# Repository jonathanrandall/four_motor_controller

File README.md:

# NOTE

This was originally done in kicad 9.0 and updated to kicad 10.0. Need to check the symbol for the NMOS transistor against the data sheet for the transistor in the bom file

# four_motor_controller

A 4-layer PCB motor controller for robotics applications. Drives 4 DC motors with encoder feedback using an ESP32-S3 microcontroller, 
Inlcudes:
* 4× VNH7040AYTR high-current motor drivers, which is rated for 35A, but the current is limited by the board and not the motor driver. I'm using 2oz copper on the outer layers and 1oz copper on the inner layers, so this should provide ~12A continuous current on each motor driver; and a
* MCP23017 I2C GPIO expander for direction control.

The design files are for KiCad 10.0.

The ROS2 control code used in the video is at https://github.com/jonathanrandall/new_pcb_robot

## Repository Contents

```
hardware/                   # KiCad schematic, PCB layout, and project files
  symbols/                  # Custom KiCad symbol and footprint for VNH7040AYTR
docs_and_outputs/           # BOM (JLCPCB format), Gerbers (zip), PINMAP, and datasheets
firmware/esp32_bridge/      # PlatformIO firmware project (Arduino framework, C++17)
  src/                      # main.cpp, Motor, PIDController, QuadratureEncoder,
                            #   RobotController, Mcp23017Bus, WebDashboard, PanTiltController
  include/                  # Header files
  platformio.ini            # Build configuration
```

## Important Notes

**The BOM and PINMAP in `docs_and_outputs/` may be out of date.** Always cross-reference against the schematic and PCB files before ordering parts or assembling hardware.

**The custom VNH7040AYTR symbol/footprint** (`hardware/symbols/`) must be added to your KiCad library if opening the project on a new machine.

**The firmware has not been validated on hardware.** It compiles and is provided as a starting point.

**WiFi credentials are not included.** Before building the firmware, set your SSID and password in `firmware/esp32_bridge/src/main.cpp`.

## Building the Firmware

Requires [PlatformIO](https://platformio.org/). All commands run from `firmware/esp32_bridge/`.

```bash
# Build
pio run

# Flash (USB-C, use BOOT mode if required)
pio run --target upload

# Monitor serial output (115200 baud)
pio device monitor
```

## Contributing

Contributions are welcome. If you have your own motor controller design or variant you would like to share, please add it in its own directory rather than modifying the existing files. Pull requests with bug fixes or improvements to the existing design are welcome.

## Disclaimer

This hardware design is provided as-is, with no warranty of any kind. Anyone who uses, manufactures, or builds upon these files does so entirely at their own risk. The author accepts no responsibility for any damage to property, equipment, or persons resulting from the use of this design. Always verify the design independently before fabrication or use in any application.

## Licence

The hardware design files in this repository are licensed under the
CERN Open Hardware Licence Version 2 - Permissive (CERN-OHL-P-2.0).

See the `LICENSE` file for the full licence text.

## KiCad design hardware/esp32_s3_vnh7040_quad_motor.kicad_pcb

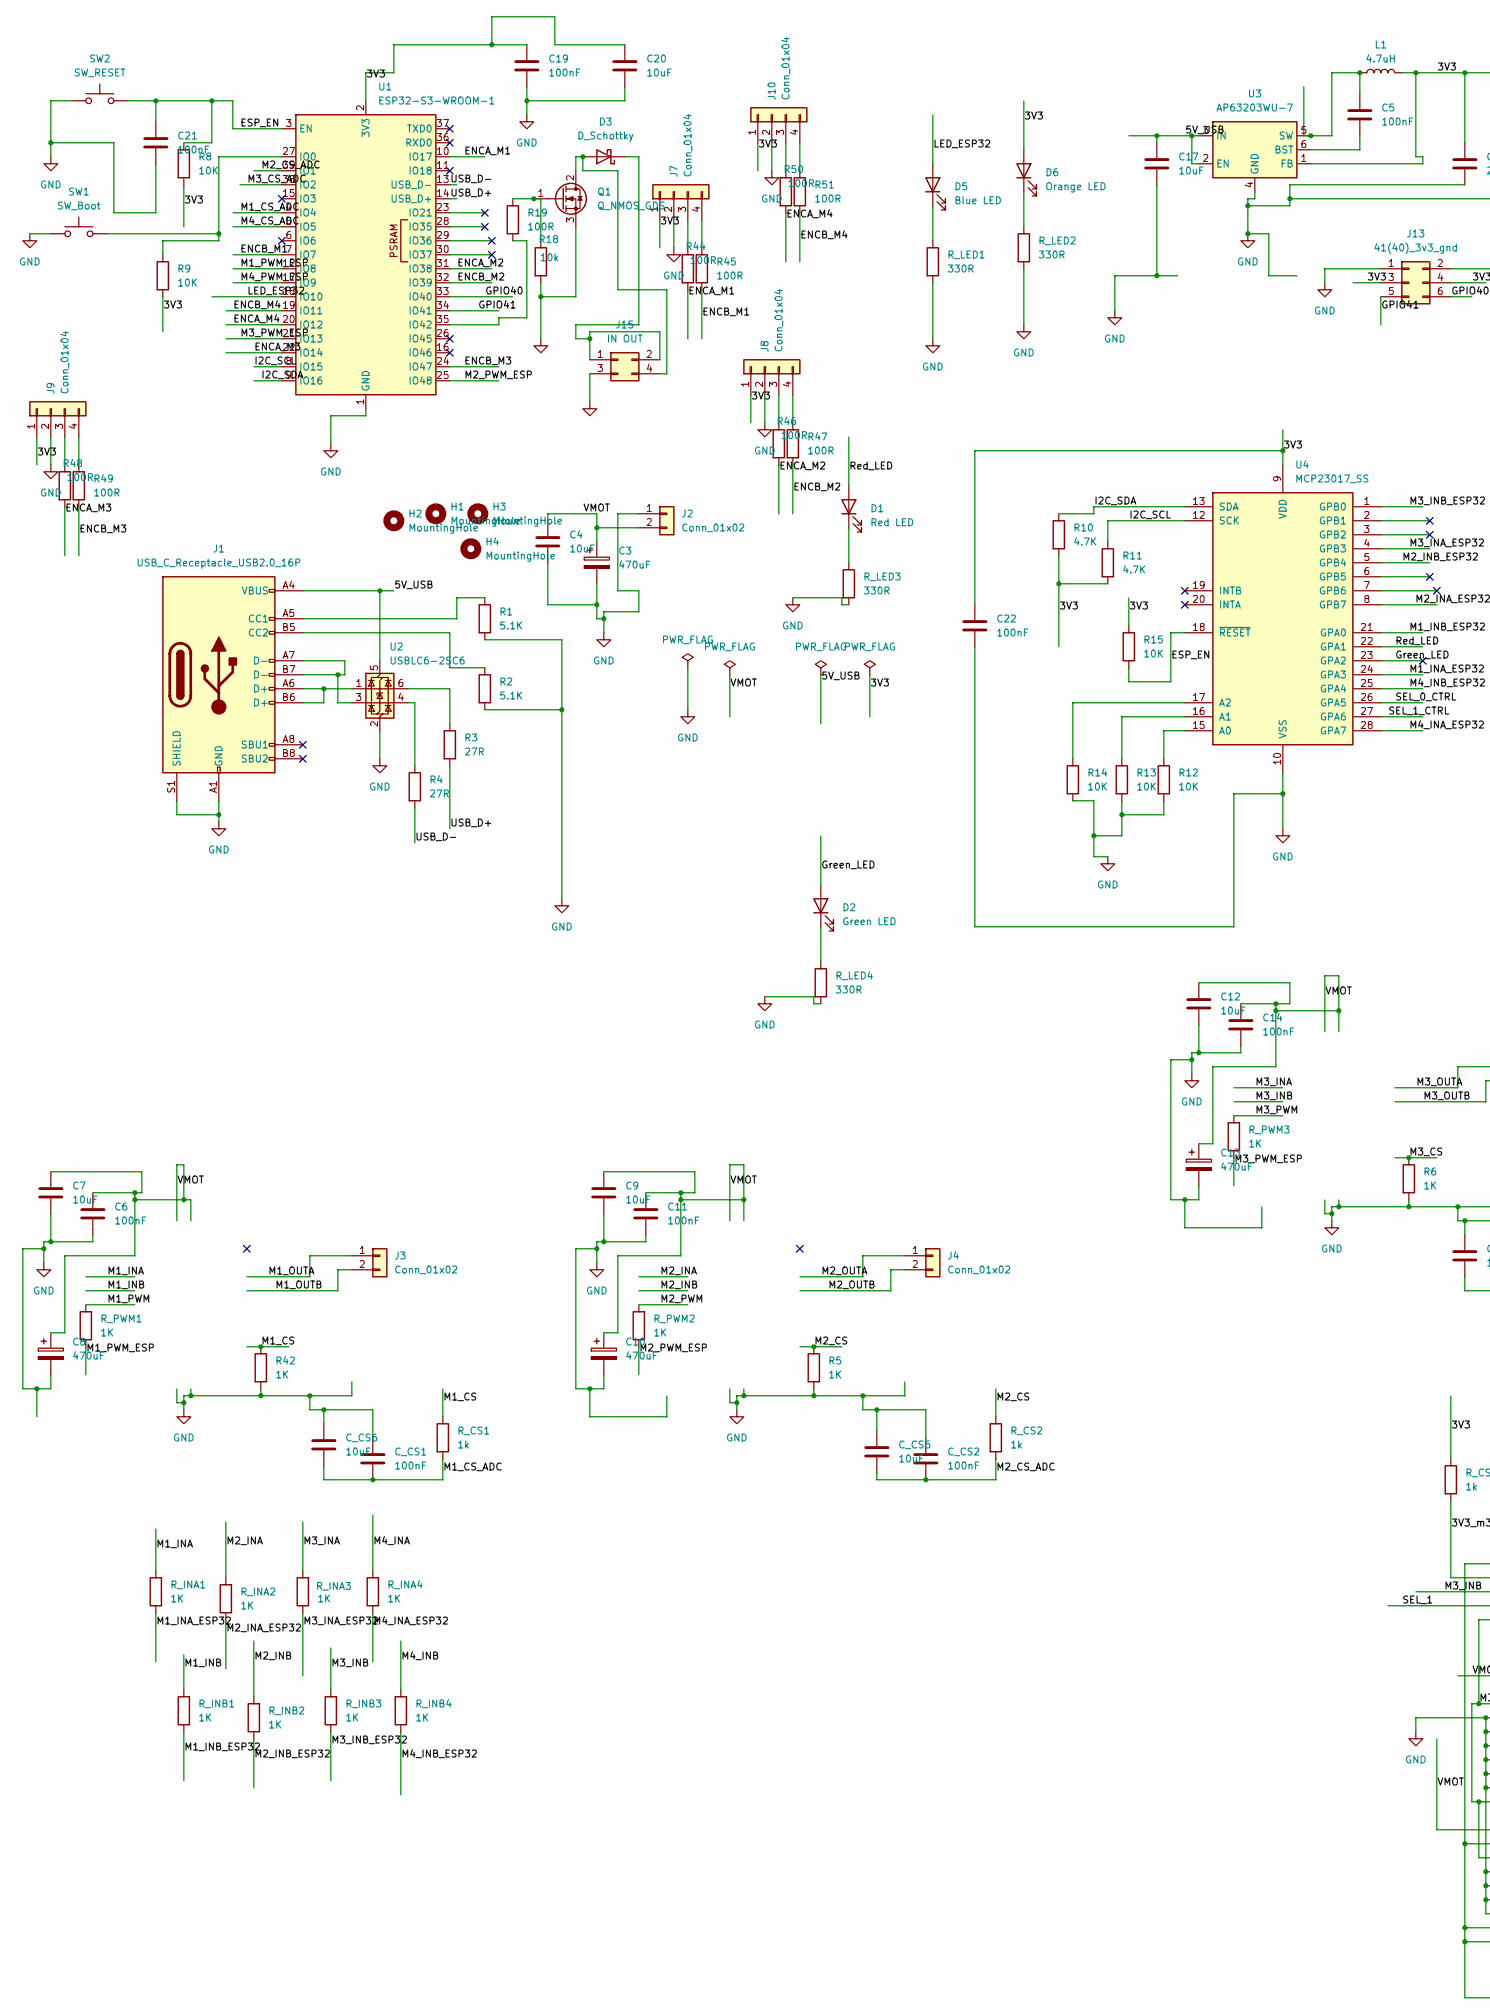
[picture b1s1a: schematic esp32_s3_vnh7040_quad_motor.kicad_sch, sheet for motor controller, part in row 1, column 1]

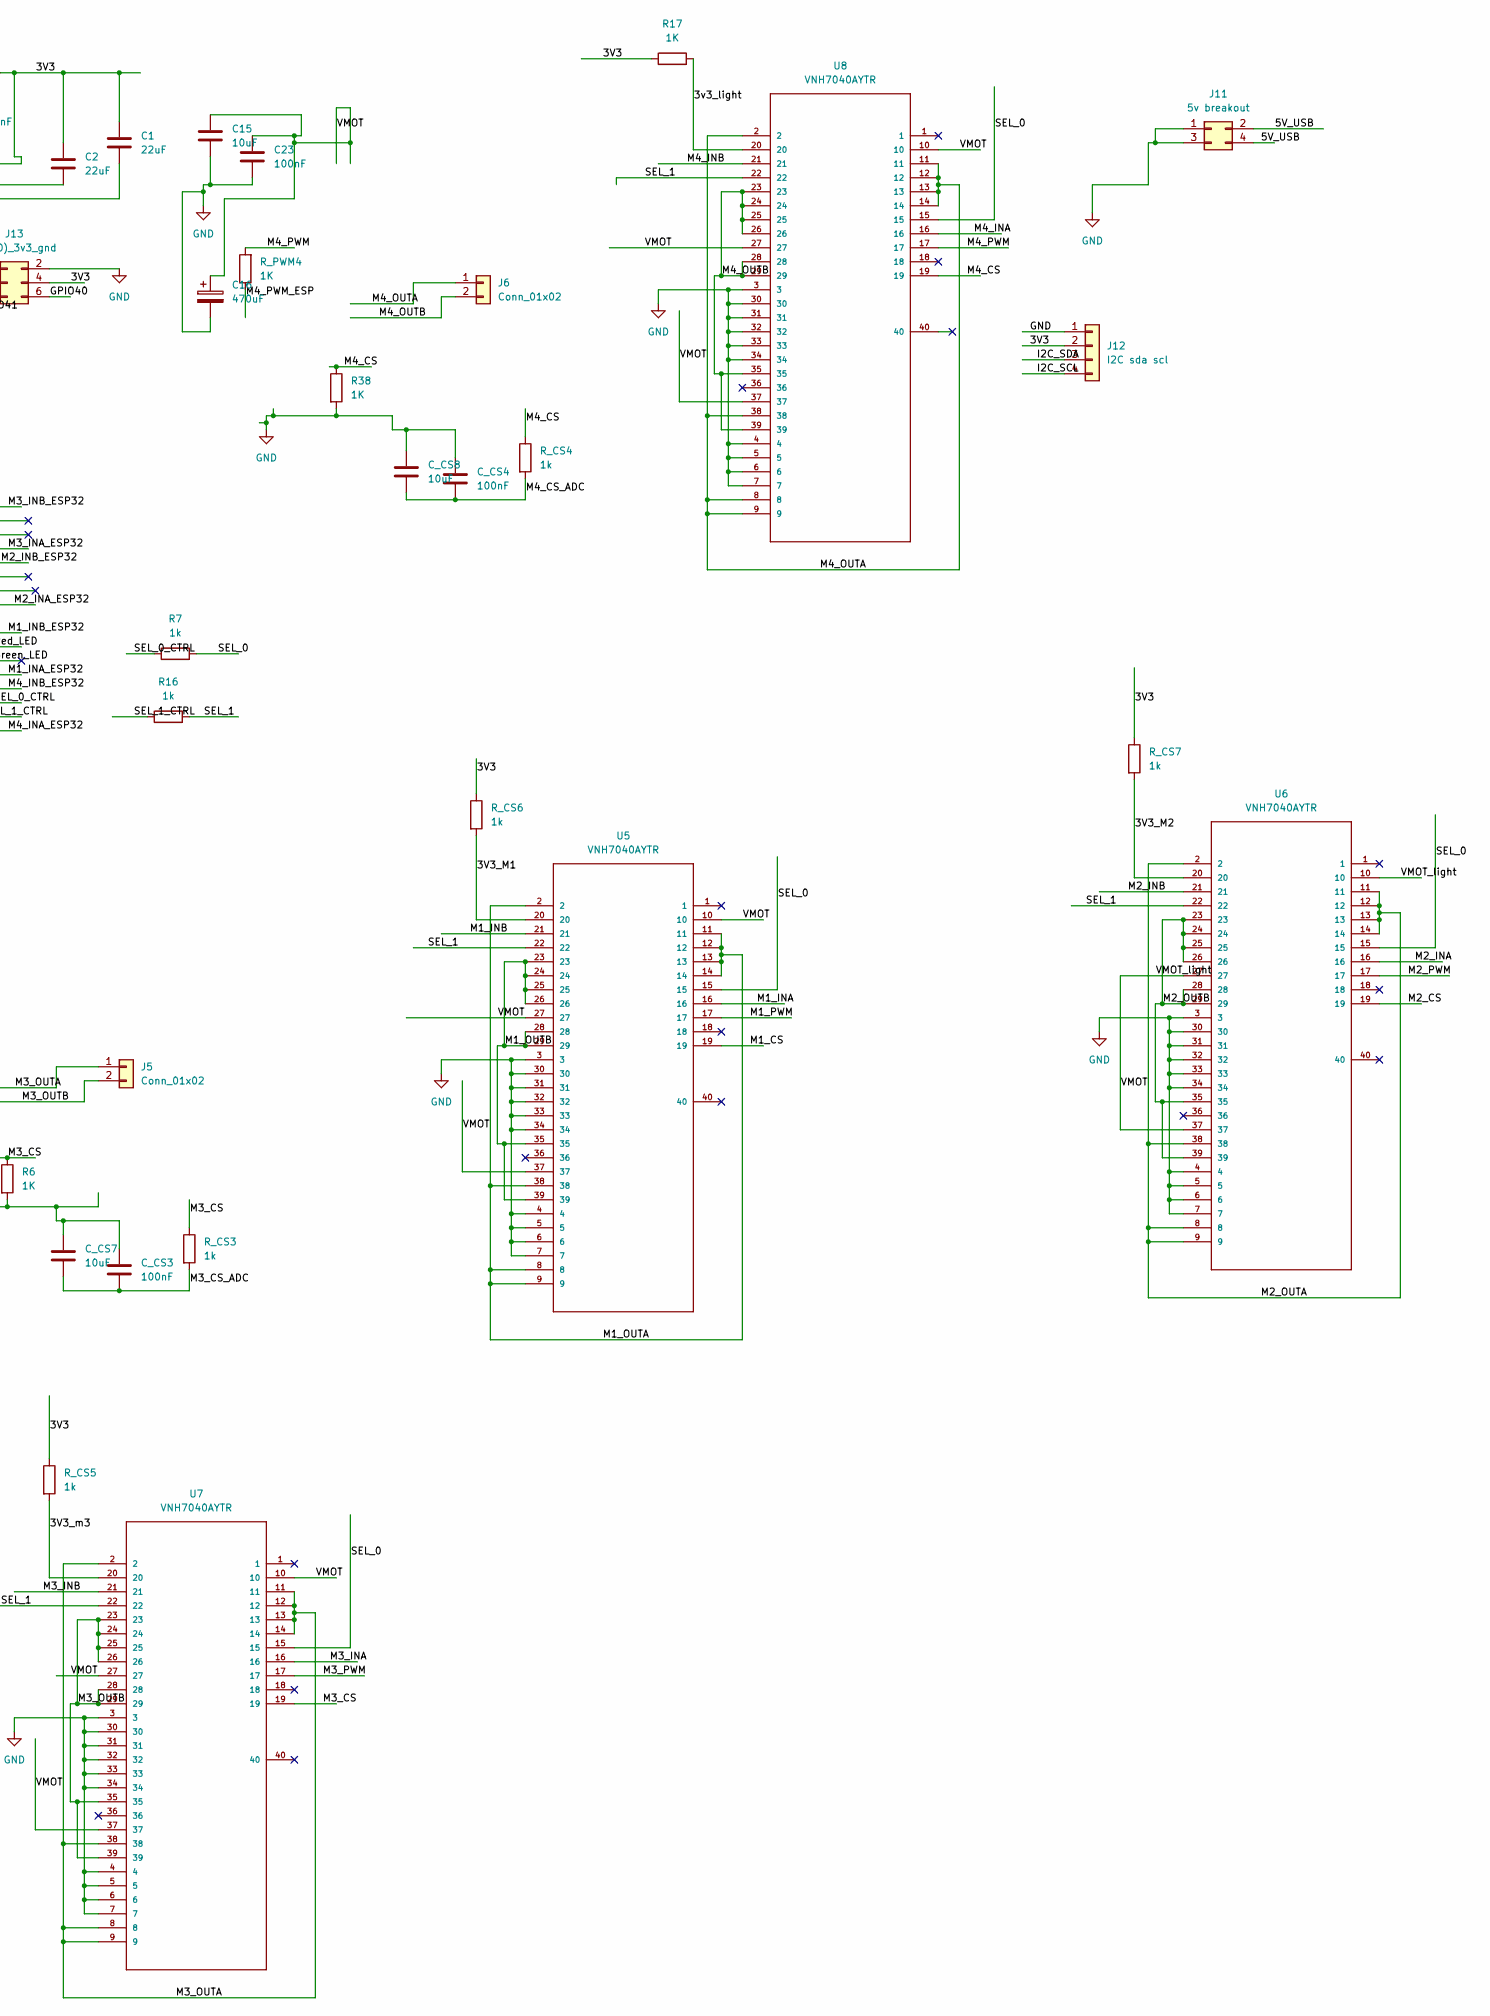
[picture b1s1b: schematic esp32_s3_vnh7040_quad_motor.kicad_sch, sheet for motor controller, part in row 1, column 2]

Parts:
C1, C2: 22uF; C_0805_2012Metric
C3, C8, C10, C13, C16: 470uF; CP_Elec_10x10
C4, C7, C9, C12, C15: 10uF; C_1206_3216Metric
C5, C6, C11, C14, C19, C21, C22, C23: 100nF; C_0805_2012Metric
C17, C20: 10uF; C_0805_2012Metric
C_CS1, C_CS2, C_CS3, C_CS4: 100nF; C_0805_2012Metric
C_CS5, C_CS6, C_CS7, C_CS8: 10uF; C_0805_2012Metric
D1: Red LED; LED_0805_2012Metric
D2: Green LED; LED_0805_2012Metric
D3: D_Schottky; D_SMA
D5: Blue LED; LED_0805_2012Metric
D6: Orange LED; LED_0805_2012Metric
H1, H2, H3, H4: MountingHole; MountingHole_3.2mm_M3
J1: USB_C_Receptacle_USB2.0_16P; USB_C_Receptacle_HRO_TYPE-C-31-M-12
J2: Conn_01x02; AMASS_XT60PW-M_1x02_P7.20mm_Horizontal
J3, J4, J5, J6: Conn_01x02; TerminalBlock_Phoenix_MKDS-3-2-5.08_1x02_P5.08mm_Horizontal
J7, J8, J9, J10: Conn_01x04; JST_XH_B4B-XH-A_1x04_P2.50mm_Vertical
J11: 5v breakout; PinHeader_2x02_P2.54mm_Vertical
J12: I2C sda scl; PinHeader_1x04_P2.54mm_Vertical
J13: 41(40)_3v3_gnd; PinHeader_2x03_P2.54mm_Vertical
J15: IN OUT; PinHeader_2x02_P2.54mm_Vertical
L1: 4.7uH; L_7.3x7.3_H4.5
Q1: Q_NMOS_GDS; SOT-23
R1, R2: 5.1K; R_0805_2012Metric
R3, R4: 27R; R_0805_2012Metric
R5, R6, R17, R38, R42: 1K; R_0805_2012Metric
R7, R16: 1k; R_0805_2012Metric
R8, R9, R12, R13, R14, R15: 10K; R_0805_2012Metric
R10, R11: 4.7K; R_0805_2012Metric
R18: 10k; R_0805_2012Metric
R19, R44, R45, R46, R47, R48, R49, R50, R51: 100R; R_0805_2012Metric
R_CS1, R_CS2, R_CS3, R_CS4, R_CS5, R_CS6, R_CS7: 1k; R_0805_2012Metric
R_INA1, R_INA2, R_INA3, R_INA4: 1K; R_0805_2012Metric
R_INB1, R_INB2, R_INB3, R_INB4: 1K; R_0805_2012Metric
R_LED1, R_LED2, R_LED3, R_LED4: 330R; R_0805_2012Metric
R_PWM1, R_PWM2, R_PWM3, R_PWM4: 1K; R_0805_2012Metric
SW1: SW_Boot; SW_SPST_TL3342
SW2: SW_RESET; SW_SPST_TL3342
U1: ESP32-S3-WROOM-1
U2: USBLC6-2SC6; SOT-23-6
U3: AP63203WU-7; TSOT-23-6-AP63203WU
U4: MCP23017_SS; SSOP-28_5.3x10.2mm_P0.65mm
U5, U6, U7, U8: VNH7040AYTR; POWERSSO-36TP_STM_jr; MANUFACTURER_PART_NUMBER VNH7040AYTR

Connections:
/3V3: C1.1, C2.1, C19.1, C20.1, C22.1, D6.2 (A), J7.1, J8.1, J9.1, J10.1, J12.2, J13.3, J13.4, L1.2, R8.2, R9.2, R10.2, R11.2, R15.1, R17.1, R_CS5.1, R_CS6.1, R_CS7.1, U1.2 (3V3), U3.1 (FB), U4.9 (VDD)
/3V3_M1: R_CS6.2, U5.20
/3V3_M2: R_CS7.2, U6.20
/3V3_m3: R_CS5.2, U7.20
/3v3_light: R17.2, U8.20
/5V_USB: C17.1, J1.A4 (VBUS), J1.A9 (VBUS), J1.B4 (VBUS), J1.B9 (VBUS), J11.2, J11.4, U2.5 (VBUS), U3.2 (EN), U3.3 (IN)
/ENCA_M1: R44.2, U1.10 (IO17)
/ENCA_M2: R46.2, U1.31 (IO38)
/ENCA_M3: R48.2, U1.22 (IO14)
/ENCA_M4: R50.2, U1.20 (IO12)
/ENCB_M1: R45.2, U1.7 (IO7)
/ENCB_M2: R47.2, U1.32 (IO39)
/ENCB_M3: R49.2, U1.24 (IO47)
/ENCB_M4: R51.2, U1.19 (IO11)
/ESP_EN: C21.1, R8.1, R15.2, SW2.2, U1.3 (EN), U4.18 (~RESET)
/GPIO40: J13.6, U1.33 (IO40)
/GPIO41: J13.5, U1.34 (IO41)
/Green_LED: D2.2 (A), U4.23 (GPA2)
/I2C_SCL: J12.4, R11.1, U1.8 (IO15), U4.12 (SCK)
/I2C_SDA: J12.3, R10.1, U1.9 (IO16), U4.13 (SDA)
/LED_ESP32: D5.2 (A), U1.18 (IO10)
/M1_CS: R42.1, R_CS1.1, U5.19
/M1_CS_ADC: C_CS1.2, C_CS6.2, R_CS1.2, U1.4 (IO4)
/M1_INA: R_INA1.2, U5.16
/M1_INA_ESP32: R_INA1.1, U4.24 (GPA3)
/M1_INB: R_INB1.2, U5.21
/M1_INB_ESP32: R_INB1.1, U4.21 (GPA0)
/M1_OUTA: J3.1, U5.2, U5.8, U5.9, U5.11, U5.12, U5.13, U5.14, U5.38
/M1_OUTB: J3.2, U5.23, U5.24, U5.25, U5.26, U5.28, U5.29, U5.35, U5.39
/M1_PWM: R_PWM1.2, U5.17
/M1_PWM_ESP: R_PWM1.1, U1.12 (IO8)
/M2_CS: R5.1, R_CS2.1, U6.19
/M2_CS_ADC: C_CS2.2, C_CS5.2, R_CS2.2, U1.39 (IO1)
/M2_INA: R_INA2.2, U6.16
/M2_INA_ESP32: R_INA2.1, U4.8 (GPB7)
/M2_INB: R_INB2.2, U6.21
/M2_INB_ESP32: R_INB2.1, U4.5 (GPB4)
/M2_OUTA: J4.1, U6.2, U6.8, U6.9, U6.11, U6.12, U6.13, U6.14, U6.38
/M2_OUTB: J4.2, U6.23, U6.24, U6.25, U6.26, U6.28, U6.29, U6.35, U6.39
/M2_PWM: R_PWM2.2, U6.17
/M2_PWM_ESP: R_PWM2.1, U1.25 (IO48)
/M3_CS: R6.1, R_CS3.1, U7.19
/M3_CS_ADC: C_CS3.2, C_CS7.2, R_CS3.2, U1.38 (IO2)
/M3_INA: R_INA3.2, U7.16
/M3_INA_ESP32: R_INA3.1, U4.4 (GPB3)
/M3_INB: R_INB3.2, U7.21
/M3_INB_ESP32: R_INB3.1, U4.1 (GPB0)
/M3_OUTA: J5.1, U7.2, U7.8, U7.9, U7.11, U7.12, U7.13, U7.14, U7.38
/M3_OUTB: J5.2, U7.23, U7.24, U7.25, U7.26, U7.28, U7.29, U7.35, U7.39
/M3_PWM: R_PWM3.2, U7.17
/M3_PWM_ESP: R_PWM3.1, U1.21 (IO13)
/M4_CS: R38.1, R_CS4.1, U8.19
/M4_CS_ADC: C_CS4.2, C_CS8.2, R_CS4.2, U1.5 (IO5)
/M4_INA: R_INA4.2, U8.16
/M4_INA_ESP32: R_INA4.1, U4.28 (GPA7)
/M4_INB: R_INB4.2, U8.21
/M4_INB_ESP32: R_INB4.1, U4.25 (GPA4)
/M4_OUTA: J6.1, U8.2, U8.8, U8.9, U8.11, U8.12, U8.13, U8.14, U8.38
/M4_OUTB: J6.2, U8.23, U8.24, U8.25, U8.26, U8.28, U8.29, U8.35, U8.39
/M4_PWM: R_PWM4.2, U8.17
/M4_PWM_ESP: R_PWM4.1, U1.17 (IO9)
/Red_LED: D1.2 (A), U4.22 (GPA1)
/SEL_0: R7.2, U5.15, U6.15, U7.15, U8.15
/SEL_0_CTRL: R7.1, U4.26 (GPA5)
/SEL_1: R16.2, U5.22, U6.22, U7.22, U8.22
/SEL_1_CTRL: R16.1, U4.27 (GPA6)
/USB_D+: R3.2, U1.14 (USB_D+)
/USB_D-: R4.2, U1.13 (USB_D-)
/VMOT: C3.1, C4.1, C6.1, C7.1, C8.1, C9.1, C10.1, C11.1, C12.1, C13.1, C14.1, C15.1, C16.1, C23.1, J2.2, U5.10, U5.27, U5.37, U6.10, U6.27, U6.37, U7.10, U7.27, U7.37, U8.10, U8.27, U8.37
unnamed: D1.1 (K), R_LED3.1
unnamed: D2.1 (K), R_LED4.1
unnamed: D3.1 (K), J15.1, J15.2
unnamed: D5.1 (K), R_LED1.1
unnamed: D6.1 (K), R_LED2.1
unnamed: J1.A5 (CC1), R1.1
unnamed: J1.B5 (CC2), R2.1
unnamed: J1.A6 (D+), J1.B6 (D+), U2.1 (I/O1)
unnamed: J1.A7 (D-), J1.B7 (D-), U2.3 (I/O2)
unnamed: J7.3, R44.1
unnamed: J7.4, R45.1
unnamed: J8.3, R46.1
unnamed: J8.4, R47.1
unnamed: J9.3, R48.1
unnamed: J9.4, R49.1
unnamed: J10.3, R50.1
unnamed: J10.4, R51.1
unnamed: Q1.1 (G), R18.1, R19.1
unnamed: R3.1, U2.6 (I/O1)
unnamed: R4.1, U2.4 (I/O2)
unnamed: R9.1, SW1.2, U1.27 (IO0)
unnamed: R19.2, U1.35 (IO42)
unnamed: C5.2, U3.6 (BST)
unnamed: C5.1, L1.1, U3.5 (SW)
unnamed: R12.1, U4.15 (A0)
unnamed: R13.1, U4.16 (A1)
unnamed: R14.1, U4.17 (A2)

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
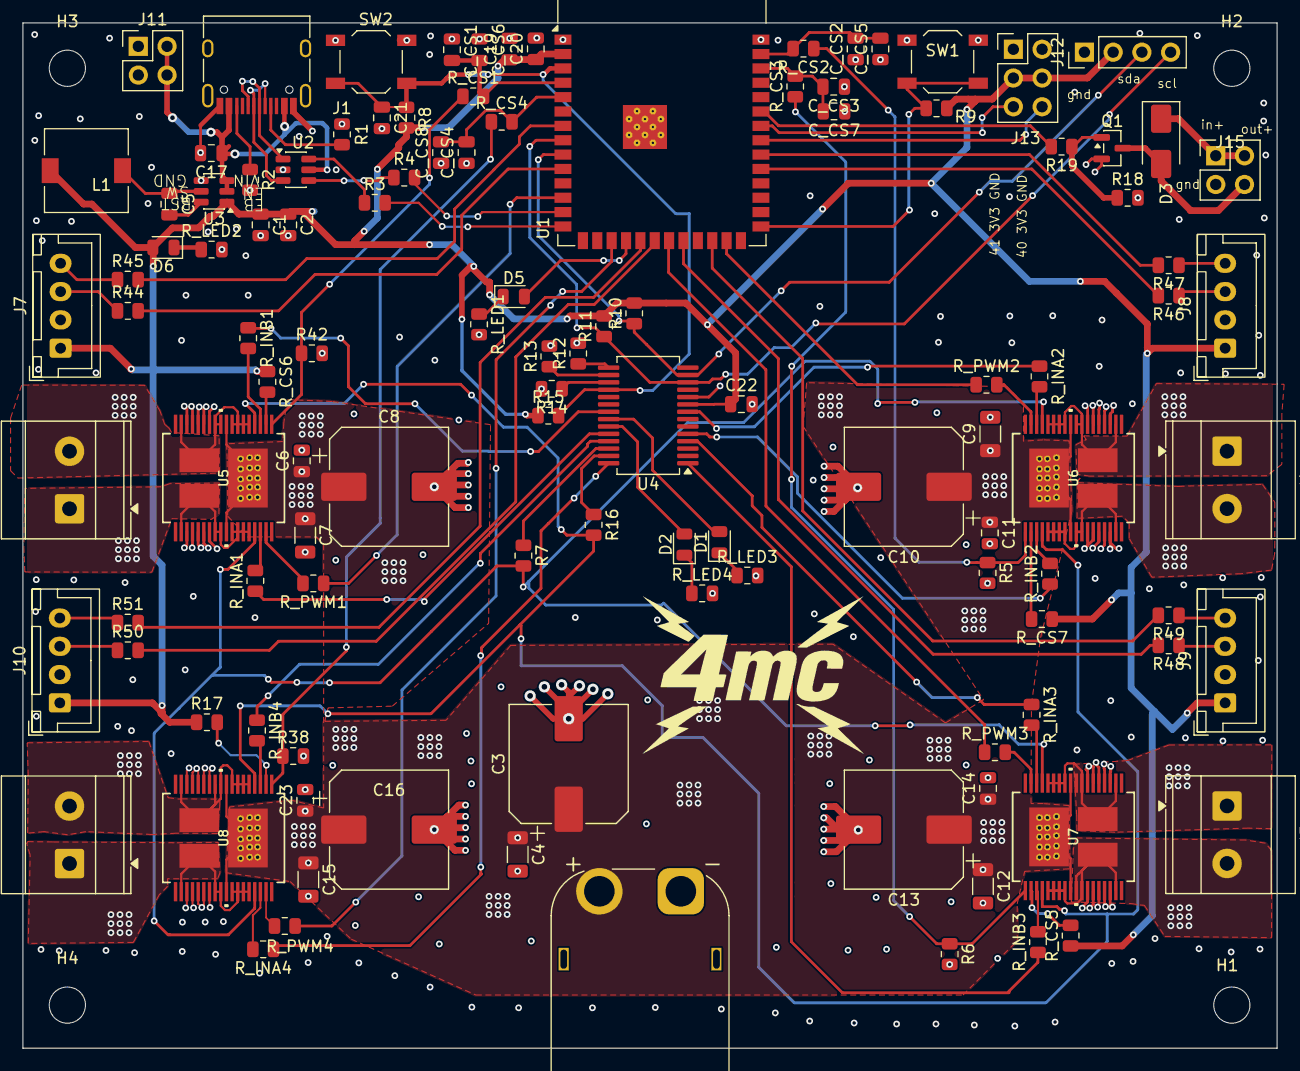
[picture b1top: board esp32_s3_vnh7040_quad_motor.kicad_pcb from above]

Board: 4 copper layers, 110.8 x 90.6 mm, 117 parts (0 on the bottom side), 98 nets.

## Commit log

2026-04-26 files
2026-04-27 Update README with contribution and license details
    Added sections for contributions and licensing information.
2026-04-27 new files
2026-04-27 new README

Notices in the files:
parts and their libraries:
COPYRIGHT: Copyright (C) 2023 Ultra Librarian. All rights reserved.
